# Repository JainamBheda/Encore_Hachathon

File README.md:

# Buck Converter Design

## Overview
This repository contains the design documentation and resources for a buck converter that steps down an input voltage of 24V to an output voltage of 5V. The design aims for an efficiency of at least 90% and is suitable for applications requiring efficient voltage regulation.

## Features
- Input Voltage: 24V (± 2% tolerance)
- Output Voltage: 5V
- Maximum Input Current: 1A
- Output Current: Up to 4A
- Efficiency: Minimum 90%
- Components Used
- Power NMOS: IRF540
- Inductor: 130 µH
- Output Capacitor: 47 µF (rated for at least 10V)
- Diode: Schottky diode rated for 5A and 30V
- Resistors: Various resistors for feedback and gate drive

## The design documentation includes:

- Component ratings and calculations (*Word_File*) folder
- Schematic design using KiCad(*Semantic*) folder
- PCB layout (*KiCAD_PCB*) folder
- Semantic diagram illustrating component relationships

## To view the design:

- Clone the repository:
```bash
git clone <https://github.com/JainamBheda/Encore_Hachathon>
```
- Open the design files in KiCad to view schematics and PCB layouts.

## Contributing
If you have suggestions or improvements, feel free to open an issue or submit a pull request.

## Acknowledgments
Texas Instruments for the reference design documentation in prbelm statements

KiCad community for providing an excellent tool for PCB design.

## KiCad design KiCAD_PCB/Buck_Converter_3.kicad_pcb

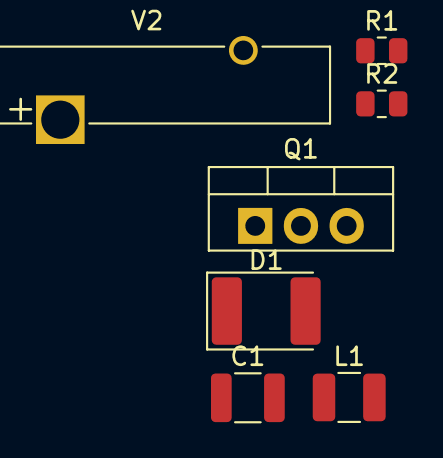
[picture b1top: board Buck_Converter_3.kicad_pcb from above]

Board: 2 copper layers, 8 parts (0 on the bottom side), 5 nets, no tracks yet.

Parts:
C1: 40.8u; C_1210_3225Metric
D1: D; D_2114_3652Metric
L1: 130u; L_1210_3225Metric
Q1: IRF540N; TO-220-3_Vertical
R1, R2: r=5; R_0805_2012Metric
V1: 24; Battery_CR1225
V2: PUL; Battery_Panasonic_CR2032-VS1N_Vertical_CircularHoles

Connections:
0: C1.2, D1.2 (A), R2.2, V2.2
/PWM_IN: R1.2, V2.1
/PWM_OUT: D1.1 (K), L1.1, Q1.3 (S)
/VOUT: C1.1, L1.2, R2.1
/gg: Q1.1 (G), R1.1

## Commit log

2024-09-26 Create temp
2024-09-26 Create a
